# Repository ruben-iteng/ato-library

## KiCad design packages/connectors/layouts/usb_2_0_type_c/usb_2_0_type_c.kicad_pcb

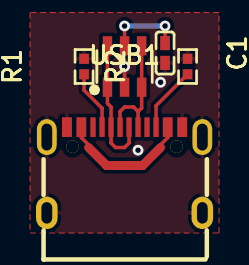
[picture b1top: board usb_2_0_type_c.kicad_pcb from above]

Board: 2 copper layers, 5 parts (0 on the bottom side), 7 nets.

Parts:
C1: 100nF ±10% 16V X7R; C0402-b3ef17
R1, R2: 5.1kΩ ±1% 62.5mW; R0402-56259e
U1: SOT-23-6_L2.9-W1.6-P0.95-LS2.8-BL-d2c740
USB1: USB-C-SMD_TYPE-C-6PIN-2MD-073-1d78f0

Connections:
CC1: R1.1, USB1.4
CC2: R2.1, USB1.10
VBUS: USB1.2, USB1.11
gnd: C1.2, R1.2, R2.2, U1.2, USB1.1, USB1.12, USB1.13, USB1.14
hv: C1.1, U1.5
line: U1.3, U1.4, USB1.6, USB1.8
line-1: U1.1, U1.6, USB1.5, USB1.7

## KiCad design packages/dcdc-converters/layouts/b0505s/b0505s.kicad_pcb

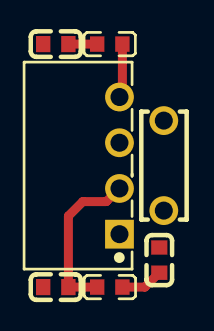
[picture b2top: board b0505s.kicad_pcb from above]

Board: 2 copper layers, 7 parts (0 on the bottom side), 6 nets.

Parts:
C1: 270pF ±10% 2kV; CAP-TH_L6.0-W2.5-P5.00-D1.0-5e41da
C2, C3: 4.7µF ±10% 10V X5R; C0603-bd72f6
C4: 10µF ±10% 10V X5R; C0603-bd72f6
L1, L2: L0603-9cac2b
U1: PWRM-TH_B0505S-1WR3-83f76b

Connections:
gnd: C1.1, C2.2, C3.2, U1.1
gnd-1: C1.2, C4.2, U1.3
hv: C2.1, L1.1
hv-1: C4.1, L2.1
hv-2: C3.1, L1.2, U1.2
hv-3: L2.2, U1.4

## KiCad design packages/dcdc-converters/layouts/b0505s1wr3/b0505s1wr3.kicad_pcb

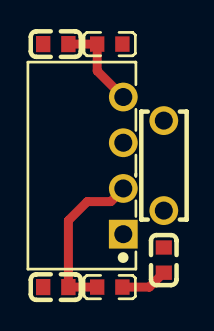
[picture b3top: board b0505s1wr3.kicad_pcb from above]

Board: 2 copper layers, 7 parts (0 on the bottom side), 5 nets.

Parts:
C1: 270pF ±10% 2kV; CAP-TH_L6.0-W2.5-P5.00-D1.0
C2, C3: 4.7nF ±10% 50V X7R; C0603
C4: 10µF ±10% 10V X5R; C0603
L1, L2: L0603
U1: PWRM-TH_B0505S-1WR3

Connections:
Vinpos: C2.1, L1.1, U1.2
Voutpos: C4.1, L2.1, U1.4
gnd: C1.1, C2.2, C3.2, U1.1
gnd-1: C1.2, C4.2, U1.3
hv: C3.1, L1.2

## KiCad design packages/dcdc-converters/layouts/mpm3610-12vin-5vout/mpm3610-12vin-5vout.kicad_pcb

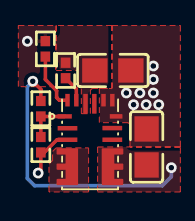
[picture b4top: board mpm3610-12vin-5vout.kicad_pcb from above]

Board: 2 copper layers, 7 parts (0 on the bottom side), 6 nets.

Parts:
C1: 10µF ±10% 25V X5R; C0805
C2: 22µF ±10% 10V X5R; C0805
R1: 53.6kΩ ±1% 62.5mW; R0402
R2, R4: 100kΩ ±1% 62.5mW; R0402
R3: 19.1kΩ ±1% 62.5mW; R0402
U1: QFN-20_L5.0-W3.0-TL-MPM3610GQV-Z

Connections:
EN_SYNC: R2.1, U1.17
FB: R3.1, R4.2, U1.1
IN: C1.1, R2.2, U1.16
OUT: C2.1, R4.1, U1.9
PG: R1.1, U1.18
gnd: C1.2, C2.2, R1.2, R3.2, U1.3, U1.12, U1.13, U1.14

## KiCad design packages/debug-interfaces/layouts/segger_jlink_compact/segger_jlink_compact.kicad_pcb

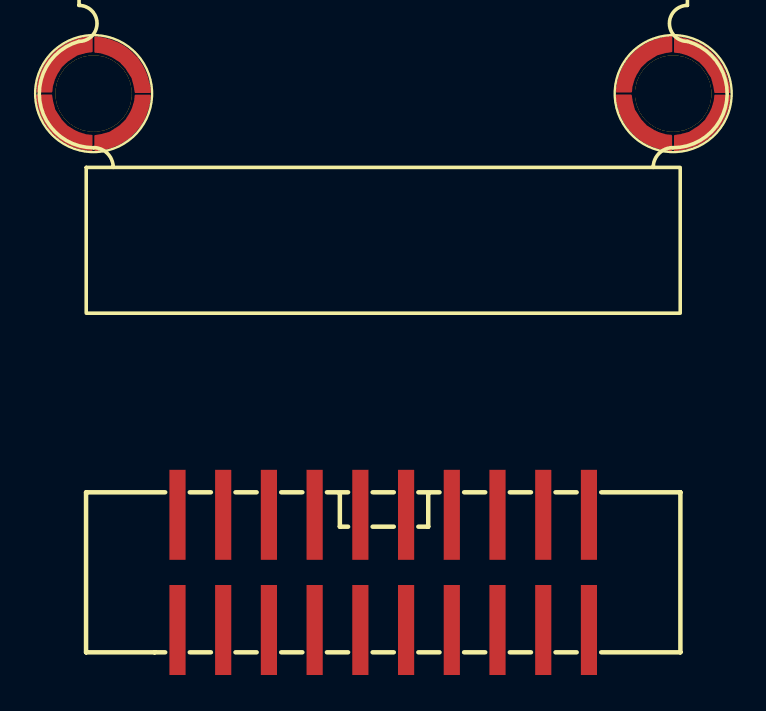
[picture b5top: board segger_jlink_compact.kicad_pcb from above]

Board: 2 copper layers, 4 parts (0 on the bottom side), 3 nets, no tracks yet.

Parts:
H1, H2: SMD_BD5.6-L5.6-W5.6-D4.1
J1: CONN-SMD_20P-P2.54_BH-00019
MOD1: SEGGER_JLink_Compact

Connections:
gnd: J1.4, J1.6, J1.8, J1.10, J1.12
standoff[0]-contact: H1.1, H1.2, H1.3, H1.4
standoff[1]-contact: H2.1, H2.2, H2.3, H2.4
